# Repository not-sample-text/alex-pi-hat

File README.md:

# Alex Pi HAT

A Raspberry Pi HAT designed as a handheld topography device, integrating multiple sensors and an OLED display for terrain mapping, elevation tracking, and environmental sensing.

## Features

- **BME280** - Temperature, humidity, and barometric pressure sensor (for altitude estimation)
- **MPU6050** - 6-axis accelerometer and gyroscope for orientation and tilt sensing
- **VL53L0X** - Time-of-Flight distance sensor (up to 2m range) for terrain profiling
- **0.96" OLED Display** - 128x64 I2C monochrome display for real-time topographic data visualization
- **User Button** - Programmable tactile switch for data capture and mode selection
- **4x M2.5 Mounting Holes** - Standard Pi HAT mechanical compatibility

## Hardware Specifications

- **Form Factor**: Raspberry Pi HAT (standard 40-pin GPIO connector)
- **Communication**: I2C bus (shared by all sensors)
- **Power**: Powered directly from Raspberry Pi 3.3V/5V rails

## Schematic & Layout

## Applications

- Handheld terrain mapping and topographic surveying
- Elevation profiling and altitude tracking
- Trail mapping and outdoor navigation
- Geological surveying
- Cave exploration and mapping
- Construction site surveys
- Environmental field research

## Design Files

This project was designed using KiCad 9.0. All design files are included:

- Schematic: `alex-pi-hat.kicad_sch`
- PCB Layout: `alex-pi-hat.kicad_pcb`
- Custom footprints and symbols in `Imports/`

## License

[Add your license here]

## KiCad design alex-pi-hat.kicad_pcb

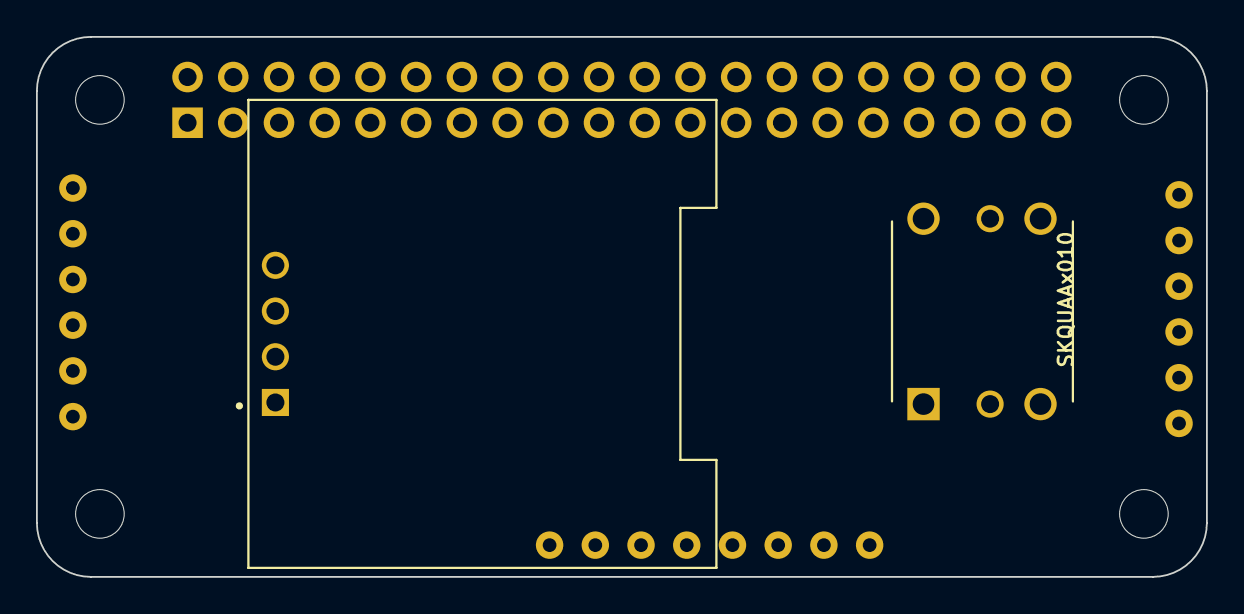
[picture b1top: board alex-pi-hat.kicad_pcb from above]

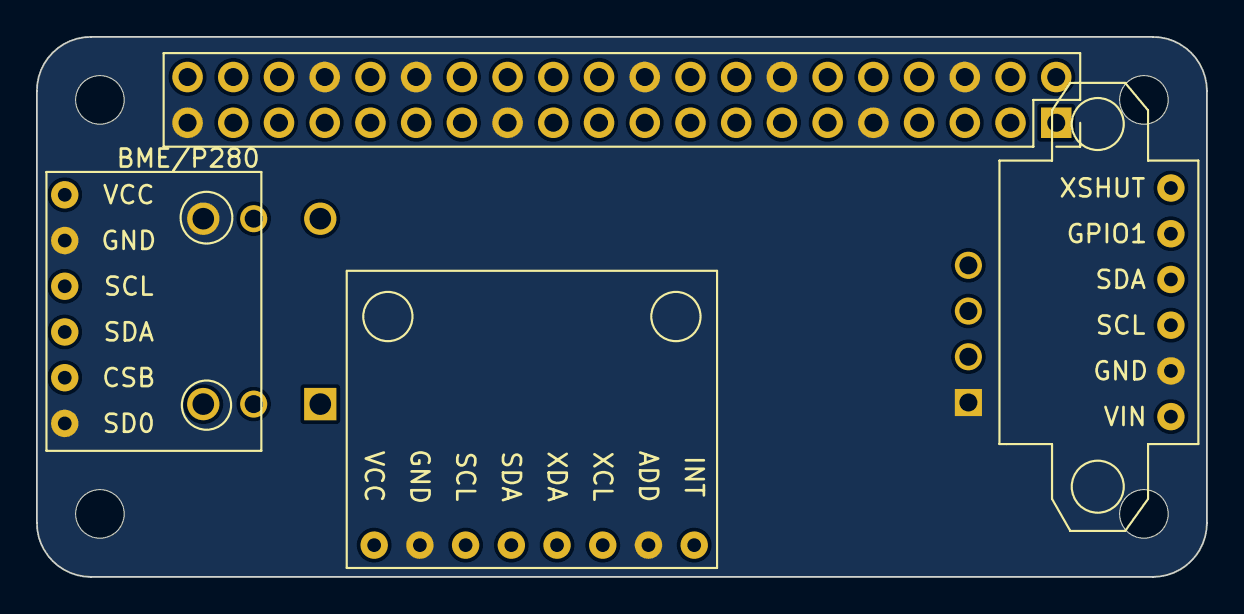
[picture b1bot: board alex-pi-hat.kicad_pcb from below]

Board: 2 copper layers, 65.0 x 30.0 mm, 10 parts (4 on the bottom side), 10 nets, no tracks yet.

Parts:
J1: GPIO; PinSocket_2x20_P2.54mm_Vertical
MH1, MH2, MH3, MH4: MountingHole_2.7mm_M2.5
U2: module_bme280
U3: module_mpu6050
U4: module_vl53L0x-v2; module_vl53l0x
U5: SKQUAAA010
U7: DM-OLED096-636; MODULE_DM-OLED096-636

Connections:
+3V3: J1.1, J1.17, U2.1 (VCC), U2.5 (CSB), U3.1 (VCC), U4.1 (VIN), U7.2 (VCC_IN)
+5V: J1.2, J1.4
GND: J1.6, J1.9, J1.14, J1.20, J1.25, J1.30, J1.34, J1.39, U2.2 (GND), U2.6 (SDO), U3.2 (GND), U3.7 (ADD), U4.2 (GND), U5.4 (COM), U7.1 (GND)
GPIO2/SDA1: J1.3, U2.4 (SDA), U3.4 (SDA), U4.4 (SDA), U7.4 (SDA)
GPIO3/SCL1: J1.5, U2.3 (SCL), U3.3 (SCL), U4.3 (SCL), U7.3 (SCL)
GPIO17: J1.11, U5.1 (A)
GPIO22: J1.15, U5.3 (C)
GPIO23: J1.16, U5.5 (D)
GPIO24: J1.18, U5.6 (PUSH)
GPIO27: J1.13, U5.2 (B)
